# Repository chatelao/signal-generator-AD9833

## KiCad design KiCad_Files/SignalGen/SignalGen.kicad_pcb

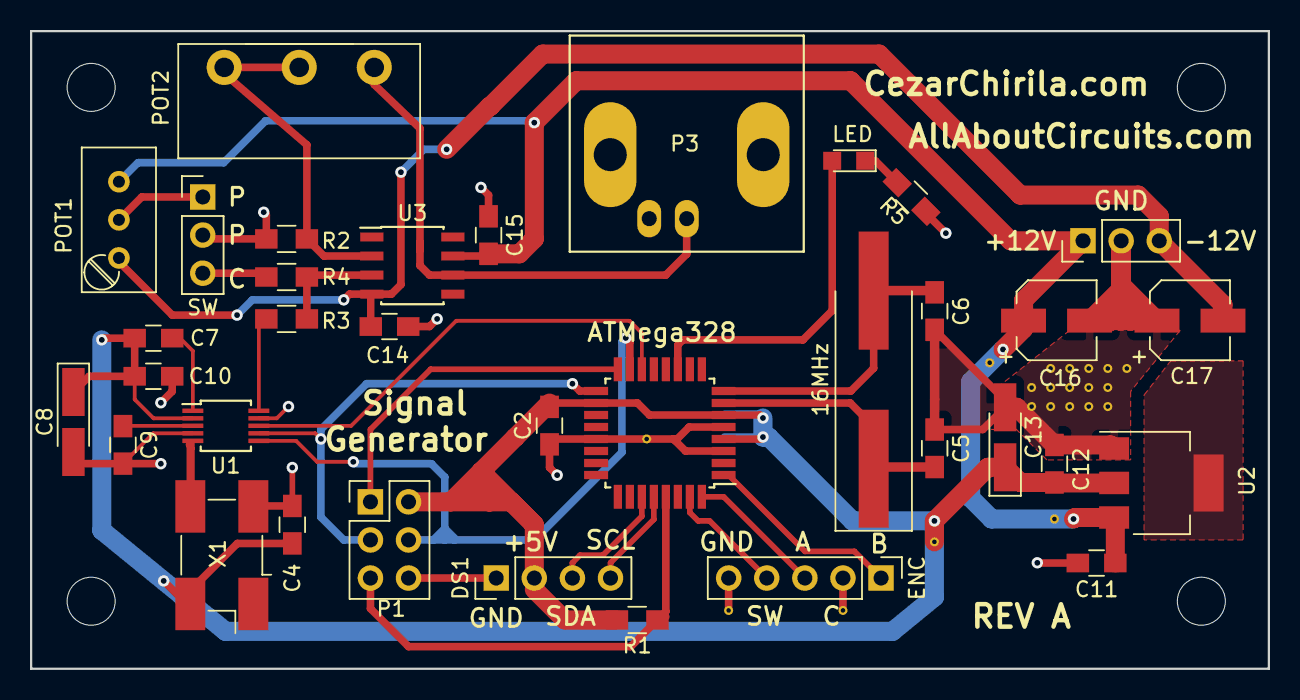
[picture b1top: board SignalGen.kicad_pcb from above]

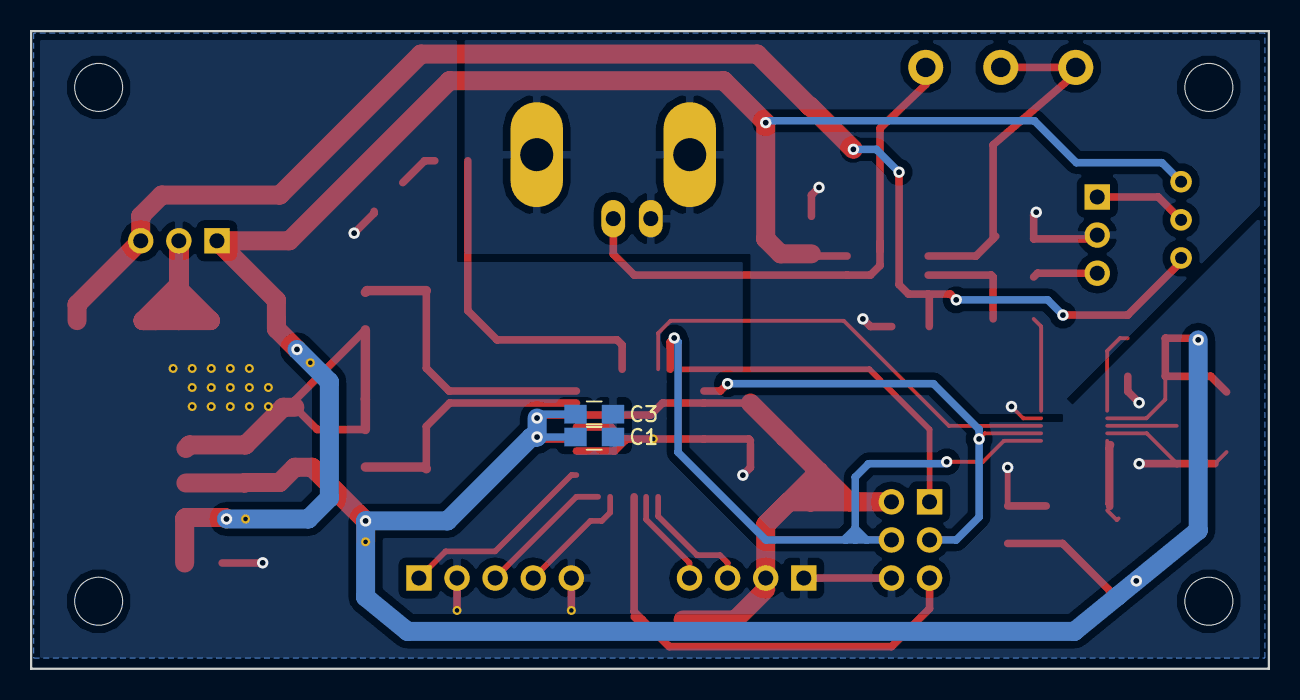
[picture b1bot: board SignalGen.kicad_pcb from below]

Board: 2 copper layers, 82.5 x 42.5 mm, 37 parts (2 on the bottom side), 27 nets.

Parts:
16MHz: 16MHz; Crystal_SMD_HC49-SD_HandSoldering
ATMega328: ATMEGA328-A; TQFP-32_7x7mm_Pitch0.8mm
C1, C2, C3, C4, C7, C9, C11, C12, C14, C15: 100n; C_0805_HandSoldering
C5, C6: 22p; C_0805_HandSoldering
C8: 10uF; CP_Tantalum_Case-A_EIA-3216-18_Hand
C10: 10n; C_0805_HandSoldering
C13: 10uf/10V; CP_Tantalum_Case-A_EIA-3216-18_Hand
C16, C17: 10uF/25V; CP_Elec_5x5.3
DS1: LCD16X2_I2C; Pin_Header_Straight_1x04_Pitch2.54mm
ENC: Rotary_Encoder_Switch; Pin_Header_Straight_1x05_Pitch2.54mm
LED: LED; LED_0805
P1: AVR-ICSP; Pin_Header_Straight_2x03_Pitch2.54mm
P2: POWER SUPPLY; Pin_Header_Straight_1x03_Pitch2.54mm
P3: Output; BNC_Socket_TYCO-AMP_LargePads
POT1: 1K; Potentiometer_Trimmer_Bourns_3296W
POT2: 100K; Potentiometer_Piher_T16H_Single_Vertical
R1: 10K; R_0805_HandSoldering
R2, R3, R4: 1K3; R_0805_HandSoldering
R5: 200; R_0805_HandSoldering
SW: SW_SPDT; Pin_Header_Straight_1x03_Pitch2.54mm
U1: AD9833BRMZ; MSOP-10_3x3mm_Pitch0.5mm
U2: TS1117-5; SOT-223
U3: LM318N; SOIC-8_3.9x4.9mm_Pitch1.27mm
X1: CFPS-72-24MHz; Oscillator_SMD_EuroQuartz_XO91-4pin_7.0x5.0mm_HandSoldering

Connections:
+5V: ATMega328.4, ATMega328.6, ATMega328.18, C1.1, C2.1, C3.1, C4.1, C7.1, C10.2, C12.1, C13.1, DS1.2, P1.2, R1.2, U1.2, U2.2, U2.4, X1.4
+12V: C11.1, C15.2, C16.1, P2.1, POT1.3, U2.3, U3.7
-12V: C14.1, C17.2, P2.3, POT1.1, U3.4
FSYNC: ATMega328.14, U1.8
GND: ATMega328.3, ATMega328.5, ATMega328.21, C1.2, C2.2, C3.2, C4.2, C5.2, C6.2, C7.2, C8.2, C9.2, C11.2, C12.2, C13.2, C14.2, C15.1, C16.2, C17.1, DS1.1, ENC.2, ENC.5, P1.6, P2.2, P3.2, R2.2, R5.1, SW.3, U1.4, U1.9, U2.1, X1.2
MISO: ATMega328.16, P1.1
unnamed: C8.1, C9.1, U1.3
unnamed: C10.1, U1.1
unnamed: LED.1, R5.2
unnamed: ATMega328.11, LED.2
unnamed: ATMega328.27, DS1.3
unnamed: ATMega328.28, DS1.4
unnamed: ATMega328.1, ENC.3
unnamed: ATMega328.31, ENC.4
unnamed: ATMega328.32, ENC.1
unnamed: P3.1, POT2.2, POT2.3, U3.6
unnamed: POT1.2, SW.1
unnamed: POT2.1, R2.1, U3.2
unnamed: R3.1, R4.1, U3.3
unnamed: R3.2, U1.10
unnamed: R4.2, SW.2
unnamed: U1.5, X1.3
RESET: ATMega328.29, P1.5, R1.1
SCLK: ATMega328.17, P1.3, U1.7
SDATA: ATMega328.15, P1.4, U1.6
XTAL1: 16MHz.1, ATMega328.7, C5.1
XTAL2: 16MHz.2, ATMega328.8, C6.1

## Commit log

2024-04-12 Kopie from All-Circuits
2024-04-12 Rename LiquidCrystal_I2C.h to code/LiquidCrystal_I2C.h
